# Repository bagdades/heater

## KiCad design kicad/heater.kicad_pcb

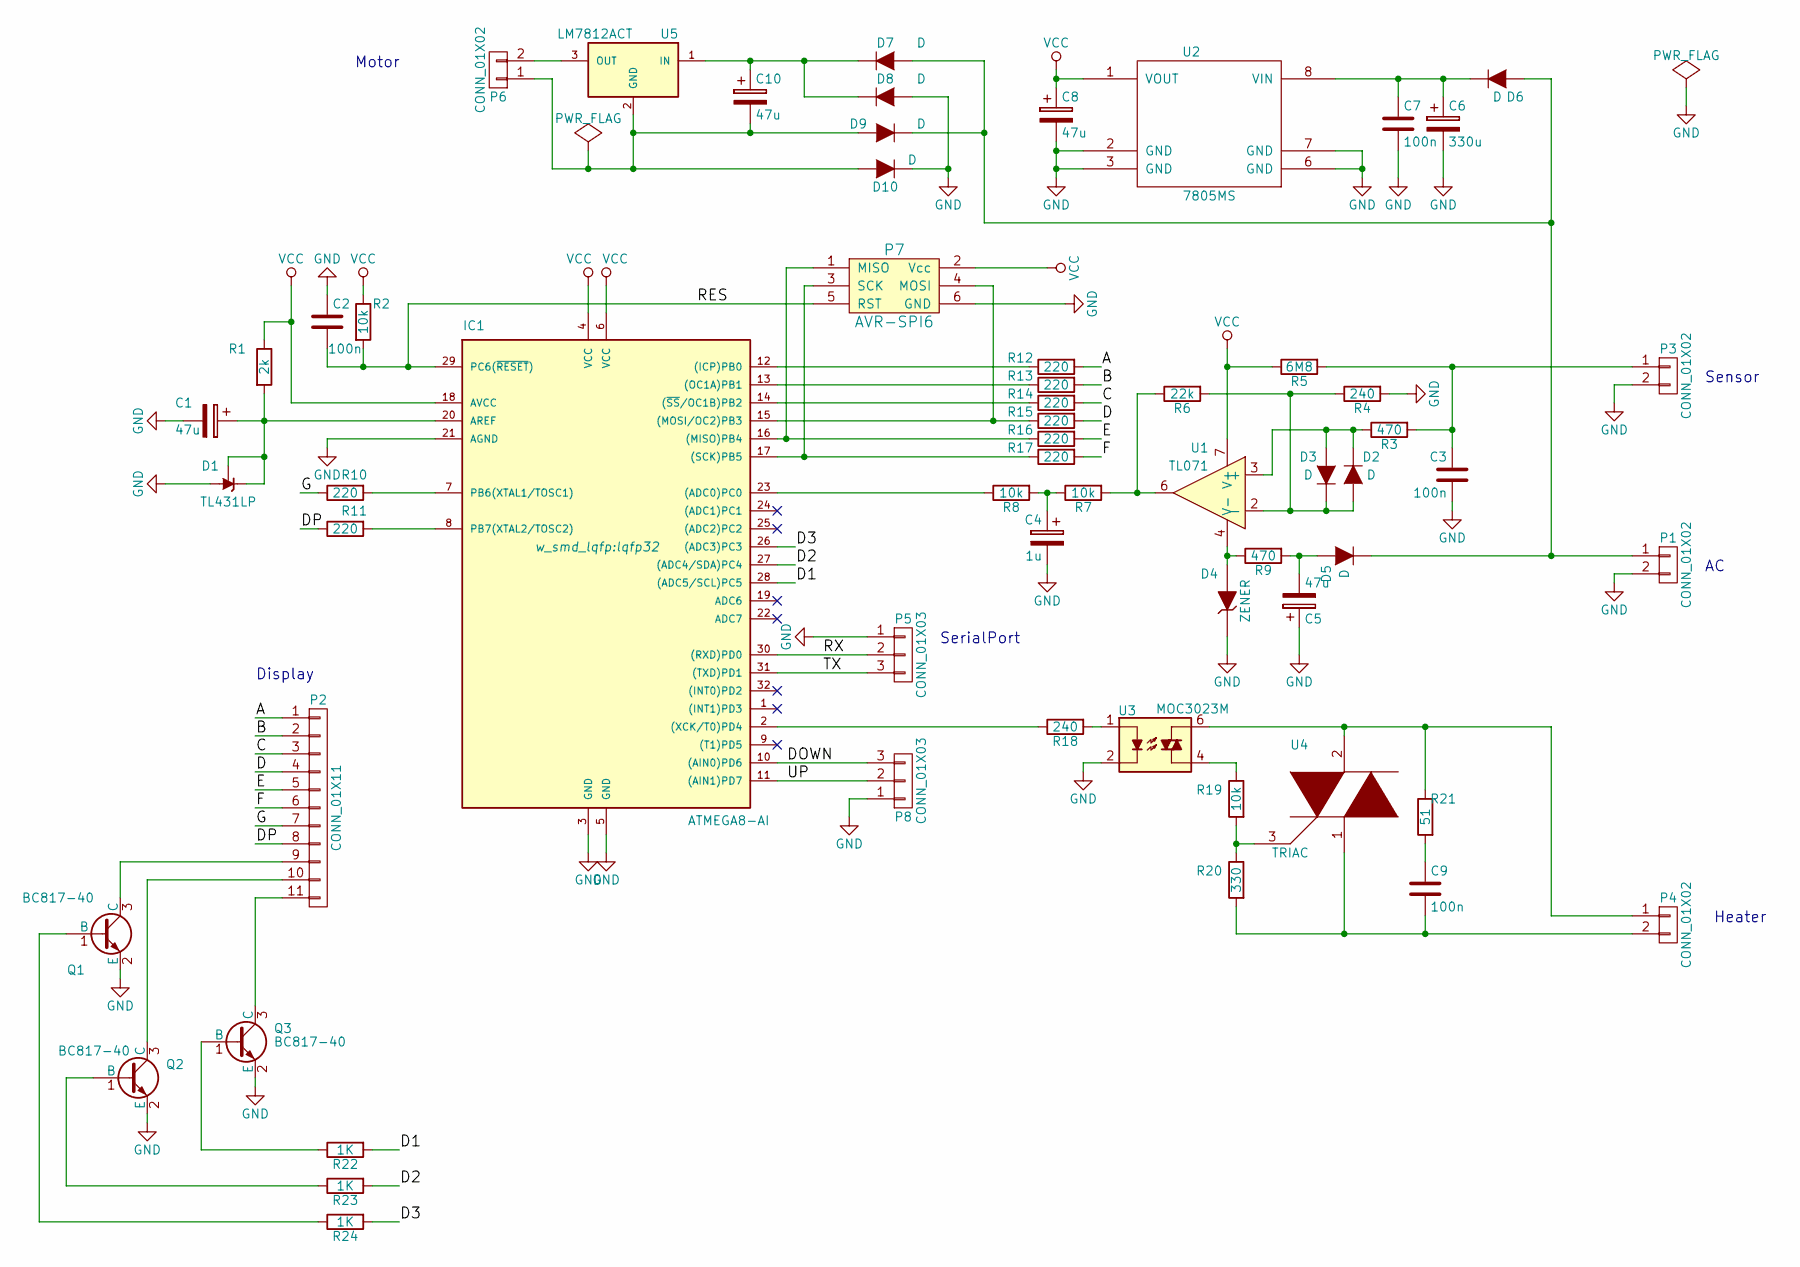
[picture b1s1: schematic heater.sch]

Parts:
C1, C5, C8, C10: 47u; Elko_vert_11.2x6.3mm_RM2.5
C2, C3, C7: 100n; c_0805
C4: 1u; Elko_vert_11.2x6.3mm_RM2.5
C6: 330u; Elko_vert_11.5x8mm_RM3.5
C9: 100n; Capacitor7x2RM5
D1: TL431LP; TO92-123
D2, D3: D; sod80c
D4: ZENER; sod80c
D5, D6, D7, D8, D9, D10: D; diode_do41
IC1: ATMEGA8-AI; lqfp32
P1, P3, P4, P6: CONN_01X02; kk100_22-23-2021
P2: CONN_01X11; pin_strip_11
P5, P8: CONN_01X03; b3b-ph-kl
P7: AVR-SPI6; Pin_Header_Straight_2x03
Q1, Q2, Q3: BC817-40; SOT-23
R1: 2k; r_0805
R2, R7, R8: 10k; r_0805
R3, R9: 470; r_0805
R4, R18: 240; r_0805
R5: 6M8; r_0805
R6: 22k; r_0805
R10, R11, R12, R13, R14, R15, R16, R17: 220; r_0805
R19: 10k; Resistor_Horizontal_RM15mm
R20: 330; Resistor_Horizontal_RM15mm
R21: 51; Resistor_Horizontal_RM15mm
R22, R23, R24: 1K; r_0805
U1: TL071; so-8
U2: 7805MS; so-8
U3: MOC3023M; DIP-6__300_ELL
U4: TRIAC; TO-220_Neutral123_Vertical
U5: LM7812ACT; TO-220_Neutral123_Vertical

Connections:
/A: P2.1, R12.2
/B: P2.2, R13.2
/C: P2.3, R14.2
/D: P2.4, R15.2
/D1: IC1.28 ((ADC5/SCL)PC5), R22.2
/D2: IC1.27 ((ADC4/SDA)PC4), R23.2
/D3: IC1.26 ((ADC3)PC3), R24.2
/DOWN: IC1.10 ((AIN0)PD6), P8.3
/DP: P2.8, R11.1
/E: P2.5, R16.2
/F: P2.6, R17.2
/G: P2.7, R10.1
/RES: C2.2, IC1.29 (PC6(~RESET~)), P7.5 (RST), R2.2
/RX: IC1.30 ((RXD)PD0), P5.2
/TX: IC1.31 ((TXD)PD1), P5.3
/UP: IC1.11 ((AIN1)PD7), P8.2
GND: C1.2, C2.1, C3.2, C4.2, C5.1, C6.2, C7.2, C8.2, D1.2 (A), D4.1 (K), D8.2 (A), D10.1 (K), IC1.3 (GND), IC1.5 (GND), IC1.21 (AGND), P1.2, P3.2, P5.1, P7.6 (GND), P8.1, Q1.2 (E), Q2.2 (E), Q3.2 (E), R4.2, U2.2 (GND), U2.3 (GND), U2.6 (GND), U2.7 (GND), U3.2
unnamed: C1.1, D1.1 (REF), D1.3 (K), IC1.20 (AREF), R1.2
unnamed: C3.1, P3.1, R3.2, R5.2
unnamed: C4.1, R7.1, R8.2
unnamed: C5.2, D5.2 (A), R9.2
unnamed: C6.1, C7.1, D6.1 (K), U2.8 (VIN)
unnamed: C9.1, R21.2
unnamed: C9.2, P4.2, R20.2, U4.1
unnamed: C10.1, D7.1 (K), D8.1 (K), U5.1 (IN)
unnamed: C10.2, D9.2 (A), D10.2 (A), P6.1, U5.2 (GND)
unnamed: D2.1 (K), D3.2 (A), R3.1, U1.3 (+)
unnamed: D2.2 (A), D3.1 (K), R4.1, R6.2, U1.2 (-)
unnamed: D4.2 (A), R9.1, U1.4 (V-)
unnamed: D5.1 (K), D6.2 (A), D7.2 (A), D9.1 (K), P1.1
unnamed: IC1.2 ((XCK/T0)PD4), R18.1
unnamed: IC1.7 (PB6(XTAL1/TOSC1)), R10.2
unnamed: IC1.8 (PB7(XTAL2/TOSC2)), R11.2
unnamed: IC1.12 ((ICP)PB0), R12.1
unnamed: IC1.13 ((OC1A)PB1), R13.1
unnamed: IC1.14 ((~SS~/OC1B)PB2), R14.1
unnamed: IC1.15 ((MOSI/OC2)PB3), P7.4 (MOSI), R15.1
unnamed: IC1.16 ((MISO)PB4), P7.1 (MISO), R16.1
unnamed: IC1.17 ((SCK)PB5), P7.3 (SCK), R17.1
unnamed: IC1.23 ((ADC0)PC0), R8.1
unnamed: P2.9, Q1.3 (C)
unnamed: P2.10, Q2.3 (C)
unnamed: P2.11, Q3.3 (C)
unnamed: P4.1, R21.1, U3.6, U4.2
unnamed: P6.2, U5.3 (OUT)
unnamed: Q1.1 (B), R24.1
unnamed: Q2.1 (B), R23.1
unnamed: Q3.1 (B), R22.1
unnamed: R6.1, R7.2, U1.6
unnamed: R18.2, U3.1
unnamed: R19.1, U3.4
unnamed: R19.2, R20.1, U4.3
VCC: C8.1, IC1.4 (VCC), IC1.6 (VCC), IC1.18 (AVCC), P7.2 (Vcc), R1.1, R2.1, R5.1, U1.7 (V+), U2.1 (VOUT)

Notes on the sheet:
Sensor
Motor
Heater
Display
SerialPort

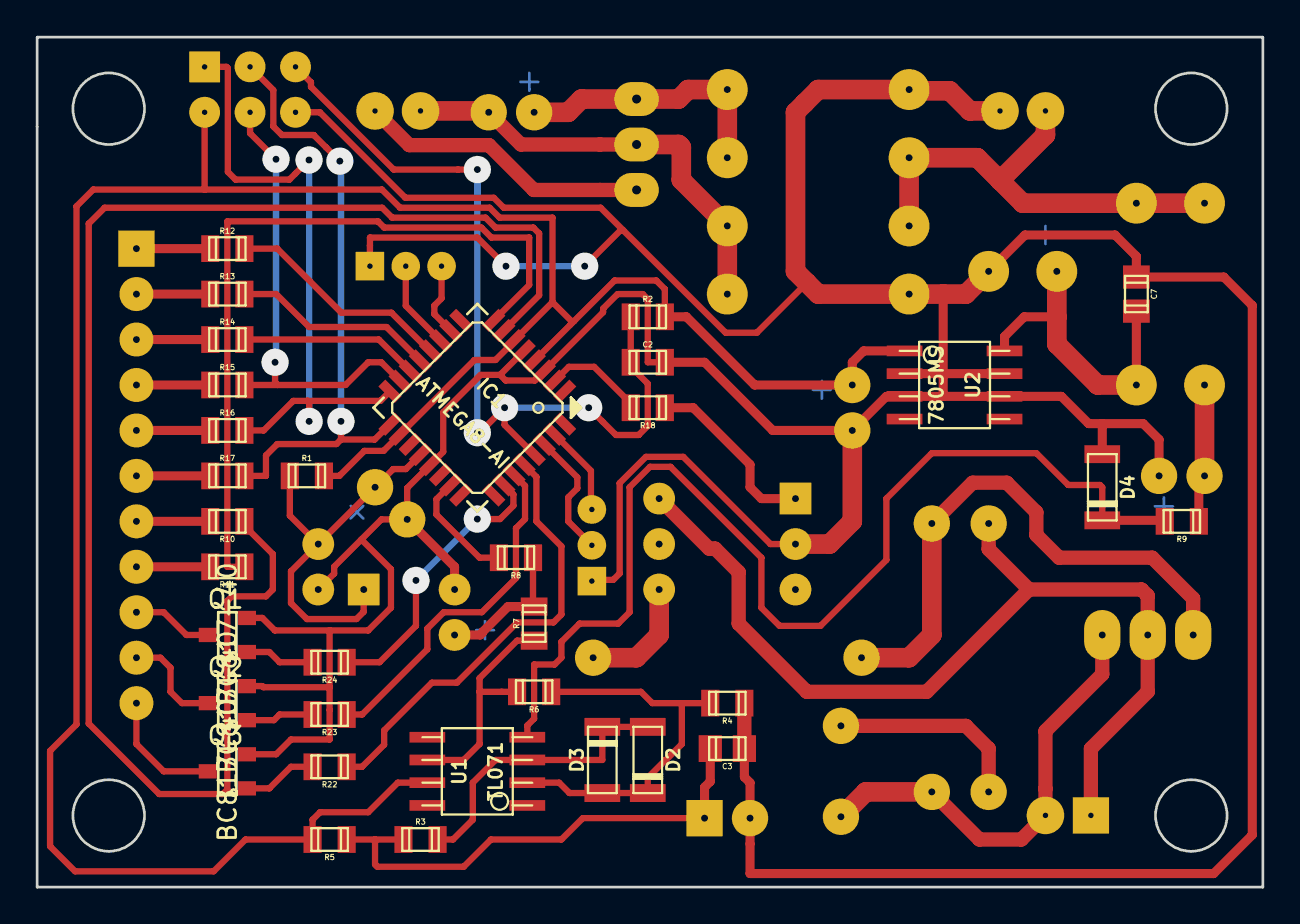
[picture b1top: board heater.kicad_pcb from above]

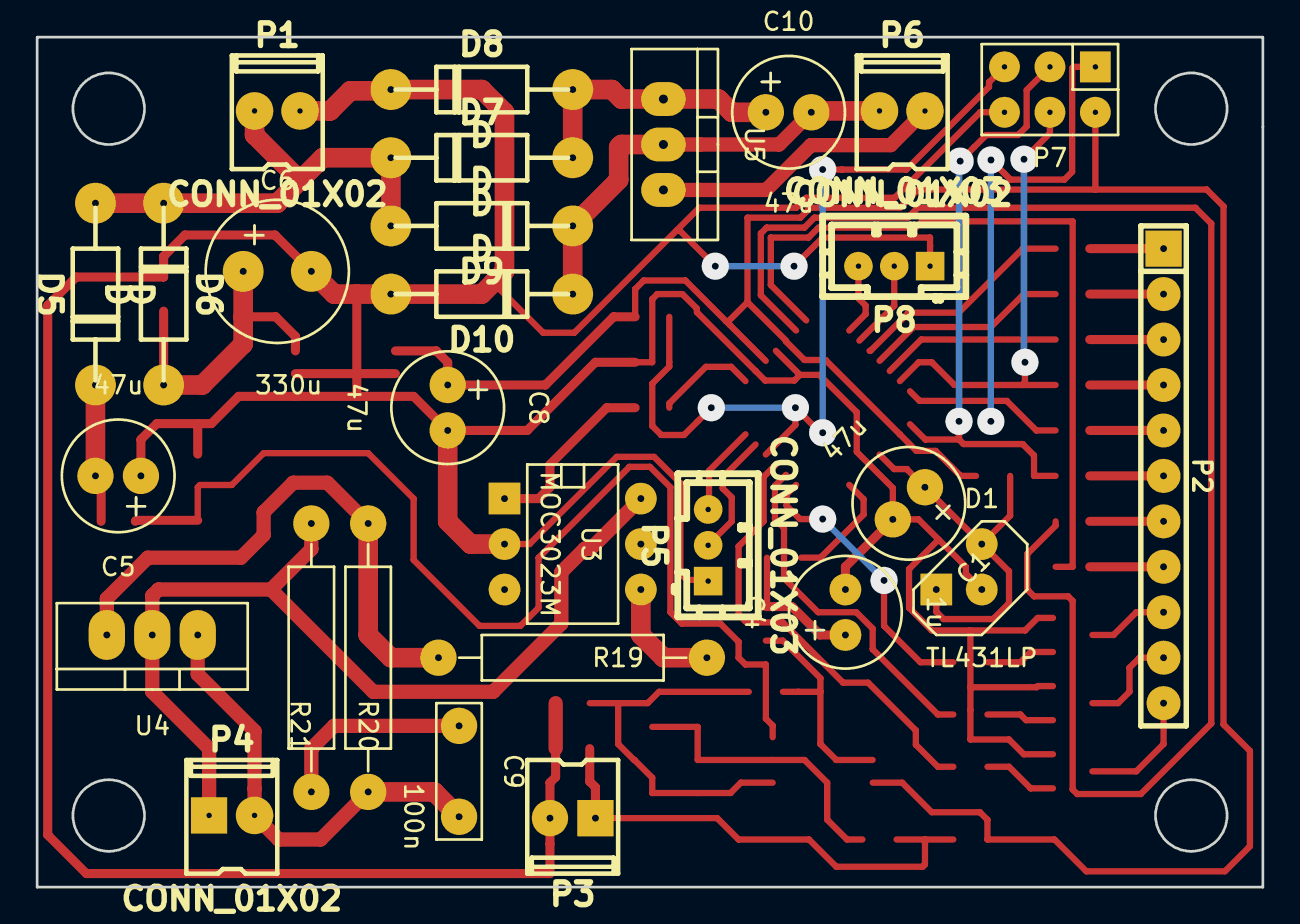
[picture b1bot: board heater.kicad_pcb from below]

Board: 2 copper layers, 68.5 x 47.5 mm, 61 parts (28 on the bottom side), 53 nets.
